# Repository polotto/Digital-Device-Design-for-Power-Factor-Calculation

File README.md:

# Digital Device Design for Power Factor Calculation

## Introduction / Introdução

This is my complete graduation thesis. My work was design and build a digial power factor meter, I used for that Tiva C microcontroller from Texas Instruments and ACS712 hall effect sensor. All the information about the measurement is displayed in a graphic serial monitor running on the computer.
All the Tiva C code was written in C language and the serial monitor was writter in Qt C++. The simulation code was written in Matlab and C ANSI.
To my thesis text, I used Latex code. All the thesis text was written in portuguse, if someone want to translate, please, fell free to do it.

## Content of This Repository

* Thesis_Polotto_TD_COELE_2015_2_026_Portuguese: PDF of my thesis in portuguse.
* Circuit Design
  * Eagle Board PDF Exported: Board design exported to PDF.
  * Eagle Board Project: Board design project made with Eagle software.
  * Multisim Simulation: Circuit simulation made with Multisim.
* Codes
  * CCS Texas Tiva C Code: Code in C written to Tiva C board, I used the CCS Texas Instruments Compiler.
  * Digital Fourier Transformer Tests: Somes tests that I made to measure the FFT performance before to implemente in the Tiva C board.
  * RS232 Terminal QT C++: Graph desktop program to see the voltage and current measured by the device. 
  * Simulations
    * Functions Test: Test of the algorithms written in C.
    * Matlab: Algorithm tests.
* Thesis Latex: All my thesis Latex content.
* Slides: All my slides apresentation in Latex.

## Thesis Abstract in English

### Digital Device Design for Power Factor Calculation

The power factor (PF) is one of the parameters related to power quality whose inadequate values cause: increasing internal power losses and voltage drops in the facility; reduction of usable capacity of transformers and engines; heated drivers; among others. Aiming for an application in the power quality area, this study proposes the development of a device capable of measuring PF of linear and nonlinear circuits (particularly single-phase rectifiers with resistive loads). The prototype will consist of a microcontroller, a Hall effect sensor to measure current and a circuit for conditioning the voltage and current signals. The embedded software developed for the system is responsible for sampling the involved quantities and, through numerical methods, calculate PF and make it accessible to the user on an interface. The operation of meter is compared with simulation data.

## Thesis Abstract in Portuguese

### Projeto de Dispositivo Digital para Cálculo do Fator de Potência

O fator de potência (FP) é um dos parâmetros relacionados à qualidade de energia, cujos valores inadequados ocasionam: aumento das perdas elétricas internas e quedas de tensão na instalação; redução do aproveitamento da capacidade dos transformadores e motores; condutores aquecidos; entre outras. Visando uma aplicação na área de qualidade de energia, esse trabalho propõe o desenvolvimento de um dispositivo capaz de mensurar o FP de circuitos lineares e não lineares (especificamente retificadores monofásicos com cargas resistivas). O projeto do protótipo é composto por um microcontrolador, sensor de efeito _Hall_ para medida de corrente e um circuito para condicionamento dos sinais de tensão e corrente. O _software_ desenvolvido e embarcado no sistema é responsável por amostrar as grandezas envolvidas e calcular o FP, através de métodos numéricos, e torná-lo acessível ao usuário em uma interface. O funcionamento do medidor é comparado com dados de simulações.

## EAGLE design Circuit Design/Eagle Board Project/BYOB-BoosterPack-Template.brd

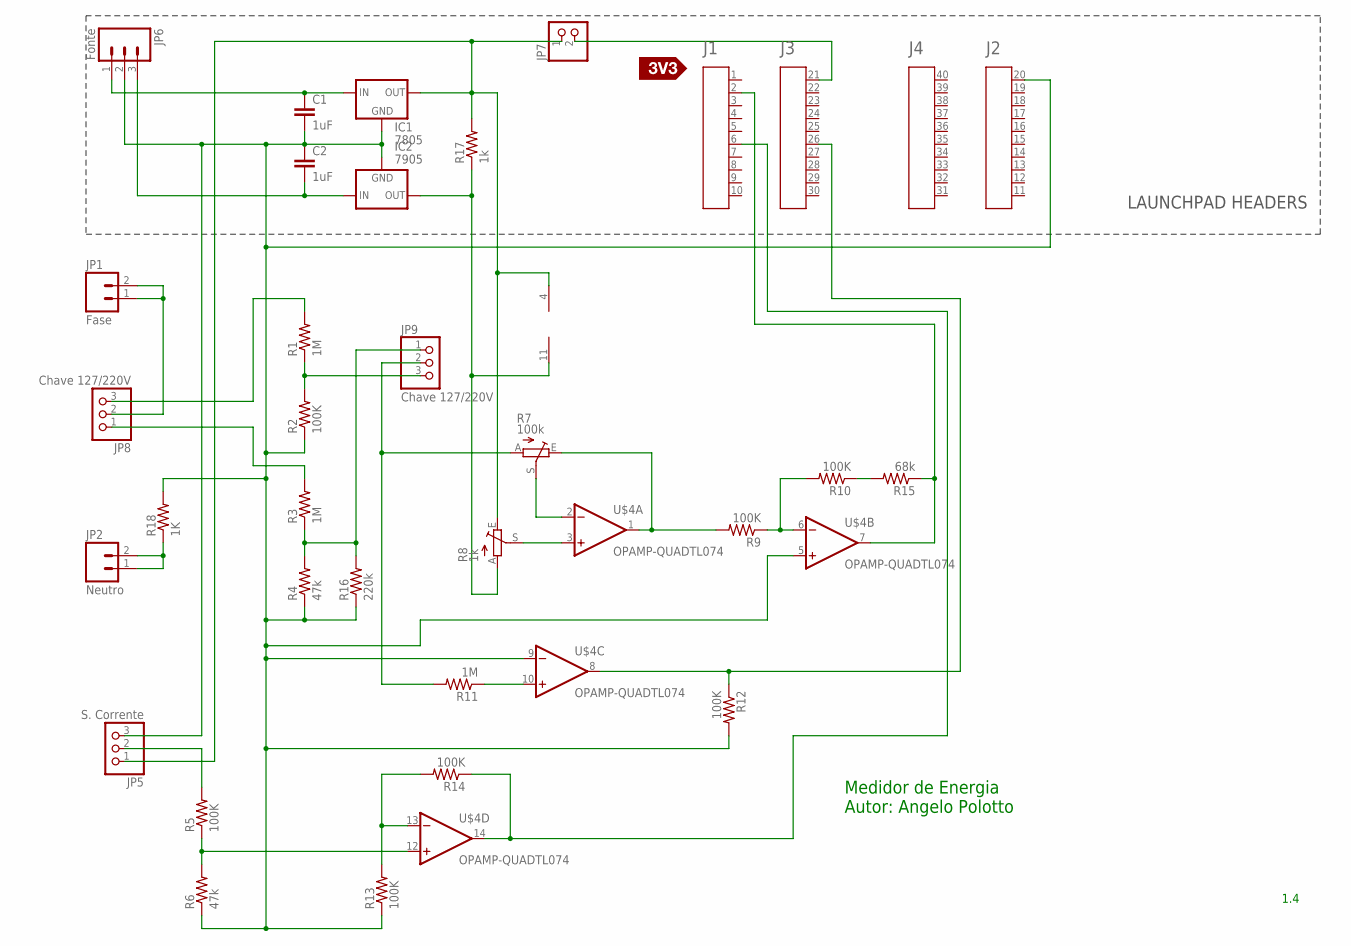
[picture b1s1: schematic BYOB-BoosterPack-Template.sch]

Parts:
A1: HEADER4X10-BOOSTERPACK; 4X10-BOOSTERPACK
C1, C2: 1uF; CAP-PTH-SMALL-KIT
IC1: 7805; 78XXS
IC2: 7905; 79XXS
JP1: Fase; 1X02_XTRA_BIG
JP2: Neutro; 1X02_XTRA_BIG
JP5: S. Corrente; 1X03
JP6: Fonte; SCREWTERMINAL-5MM-3
JP7: PINHD-1X2; 1X02
JP8, JP9: Chave 127/220V; 1X03
R1, R3, R11: 1M; AXIAL-0.3
R2, R5, R9, R10, R12, R13, R14: 100K; AXIAL-0.3
R4, R6: 47k; AXIAL-0.3
R7: 100k; B64Y
R8: 1k; B64Y
R15: 68k; AXIAL-0.3
R16: 220k; AXIAL-0.3
R17: 1k; AXIAL-0.3
R18: 1K; AXIAL-0.3
U$3: SILK_3V3_TAG
U$4: OPAMP-QUADTL074; DIP14

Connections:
GND: A1.20, C1.2, C2.1, IC1.GND, IC2.GND, JP5.3, JP6.2, R2.P$1 (1), R4.P$1 (1), R6.P$1 (1), R12.P$2 (2), R13.P$1 (1), R16.P$1 (1), R18.P$2 (2), U$4.5 (IN+), U$4.9 (IN-)
unnamed: JP9.3, R1.P$1 (1), R2.P$2 (2)
unnamed: JP9.1, R3.P$1 (1), R4.P$2 (2), R16.P$2 (2)
unnamed: R5.P$1 (1), R6.P$2 (2), U$4.12 (IN+)
unnamed: JP8.3, R1.P$2 (2)
unnamed: JP8.1, R3.P$2 (2)
unnamed: A1.21, JP7.2
unnamed: JP1.1, JP1.2, JP8.2
unnamed: JP9.2, R7.A, R11.P$2 (2)
unnamed: JP2.1, JP2.2, R18.P$1 (1)
unnamed: R7.S, U$4.2 (IN-)
unnamed: IC1.OUT, JP5.1, JP7.1, R8.E, R17.P$2 (2), U$4.4 (VCC)
unnamed: R7.E, R9.P$2 (2), U$4.1 (OUT)
unnamed: R8.S, U$4.3 (IN+)
unnamed: C1.1, IC1.IN, JP6.1
unnamed: IC2.OUT, R8.A, R17.P$1 (1), U$4.11 (VEE)
unnamed: R9.P$1 (1), R10.P$2 (2), U$4.6 (IN-)
unnamed: R10.P$1 (1), R15.P$2 (2)
unnamed: R11.P$1 (1), U$4.10 (IN+)
unnamed: A1.26, R12.P$1 (1), U$4.8 (OUT)
unnamed: JP5.2, R5.P$2 (2)
unnamed: C2.2, IC2.IN, JP6.3
unnamed: R13.P$2 (2), R14.P$2 (2), U$4.13 (IN-)
unnamed: A1.6, R14.P$1 (1), U$4.14 (OUT)
unnamed: A1.2, R15.P$1 (1), U$4.7 (OUT)

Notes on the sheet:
LAUNCHPAD HEADERS
Medidor de Energia Autor: Angelo Polotto
1.4

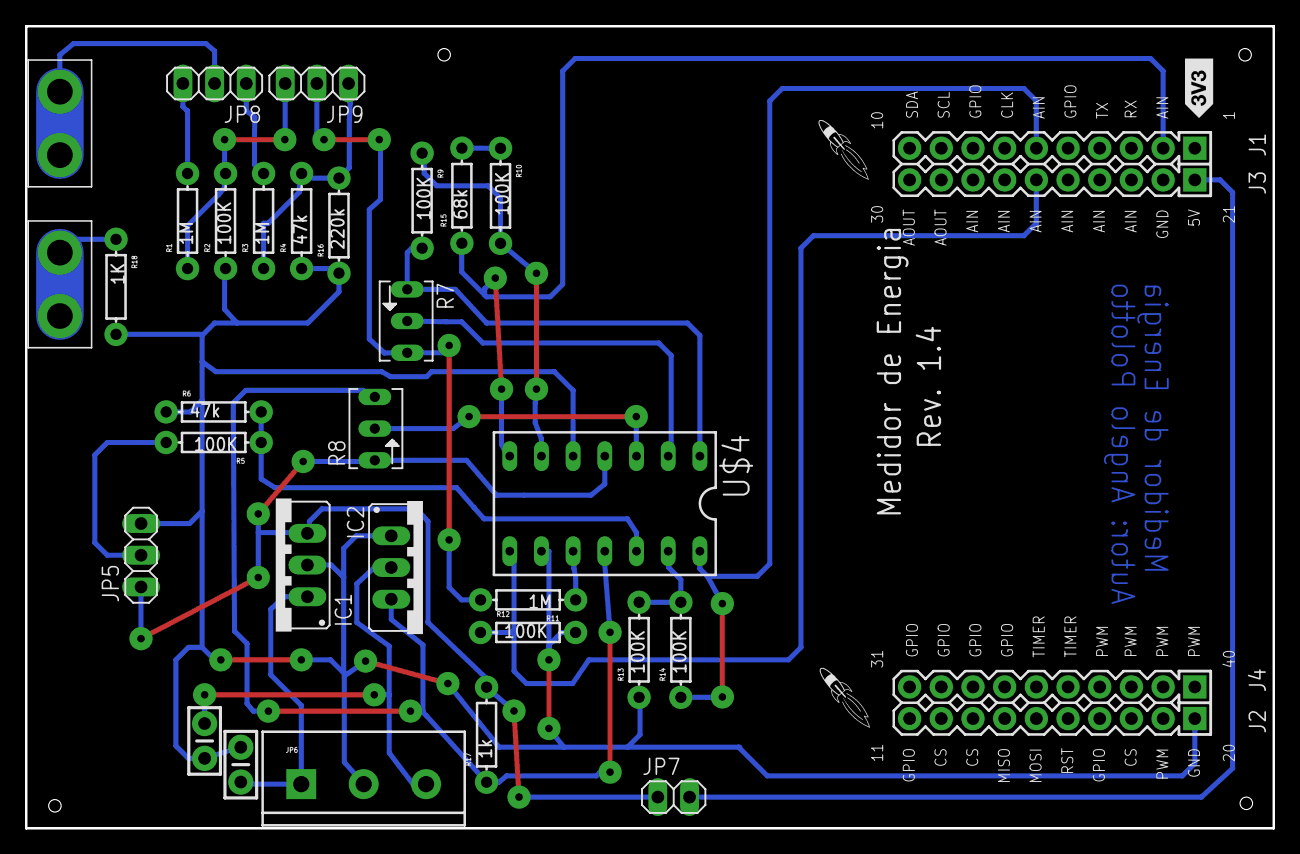
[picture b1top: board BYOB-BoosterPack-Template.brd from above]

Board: 2 copper layers, 100.0 x 64.3 mm, 34 parts (1 on the bottom side), 25 nets.

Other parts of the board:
U$1, U$2: LOGO-ROCKET

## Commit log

2017-10-17 Project files added
2017-10-17 readme updated
2017-10-17 Arquivos não necessários removidos
2017-10-17 readme fixed
2018-11-22 slided added to the repository

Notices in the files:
parts and their libraries:
SparkFun-Resistors: Licensing: Creative Commons ShareAlike 4.0 International - https://creativecommons.org/licenses/by-sa/4.0
